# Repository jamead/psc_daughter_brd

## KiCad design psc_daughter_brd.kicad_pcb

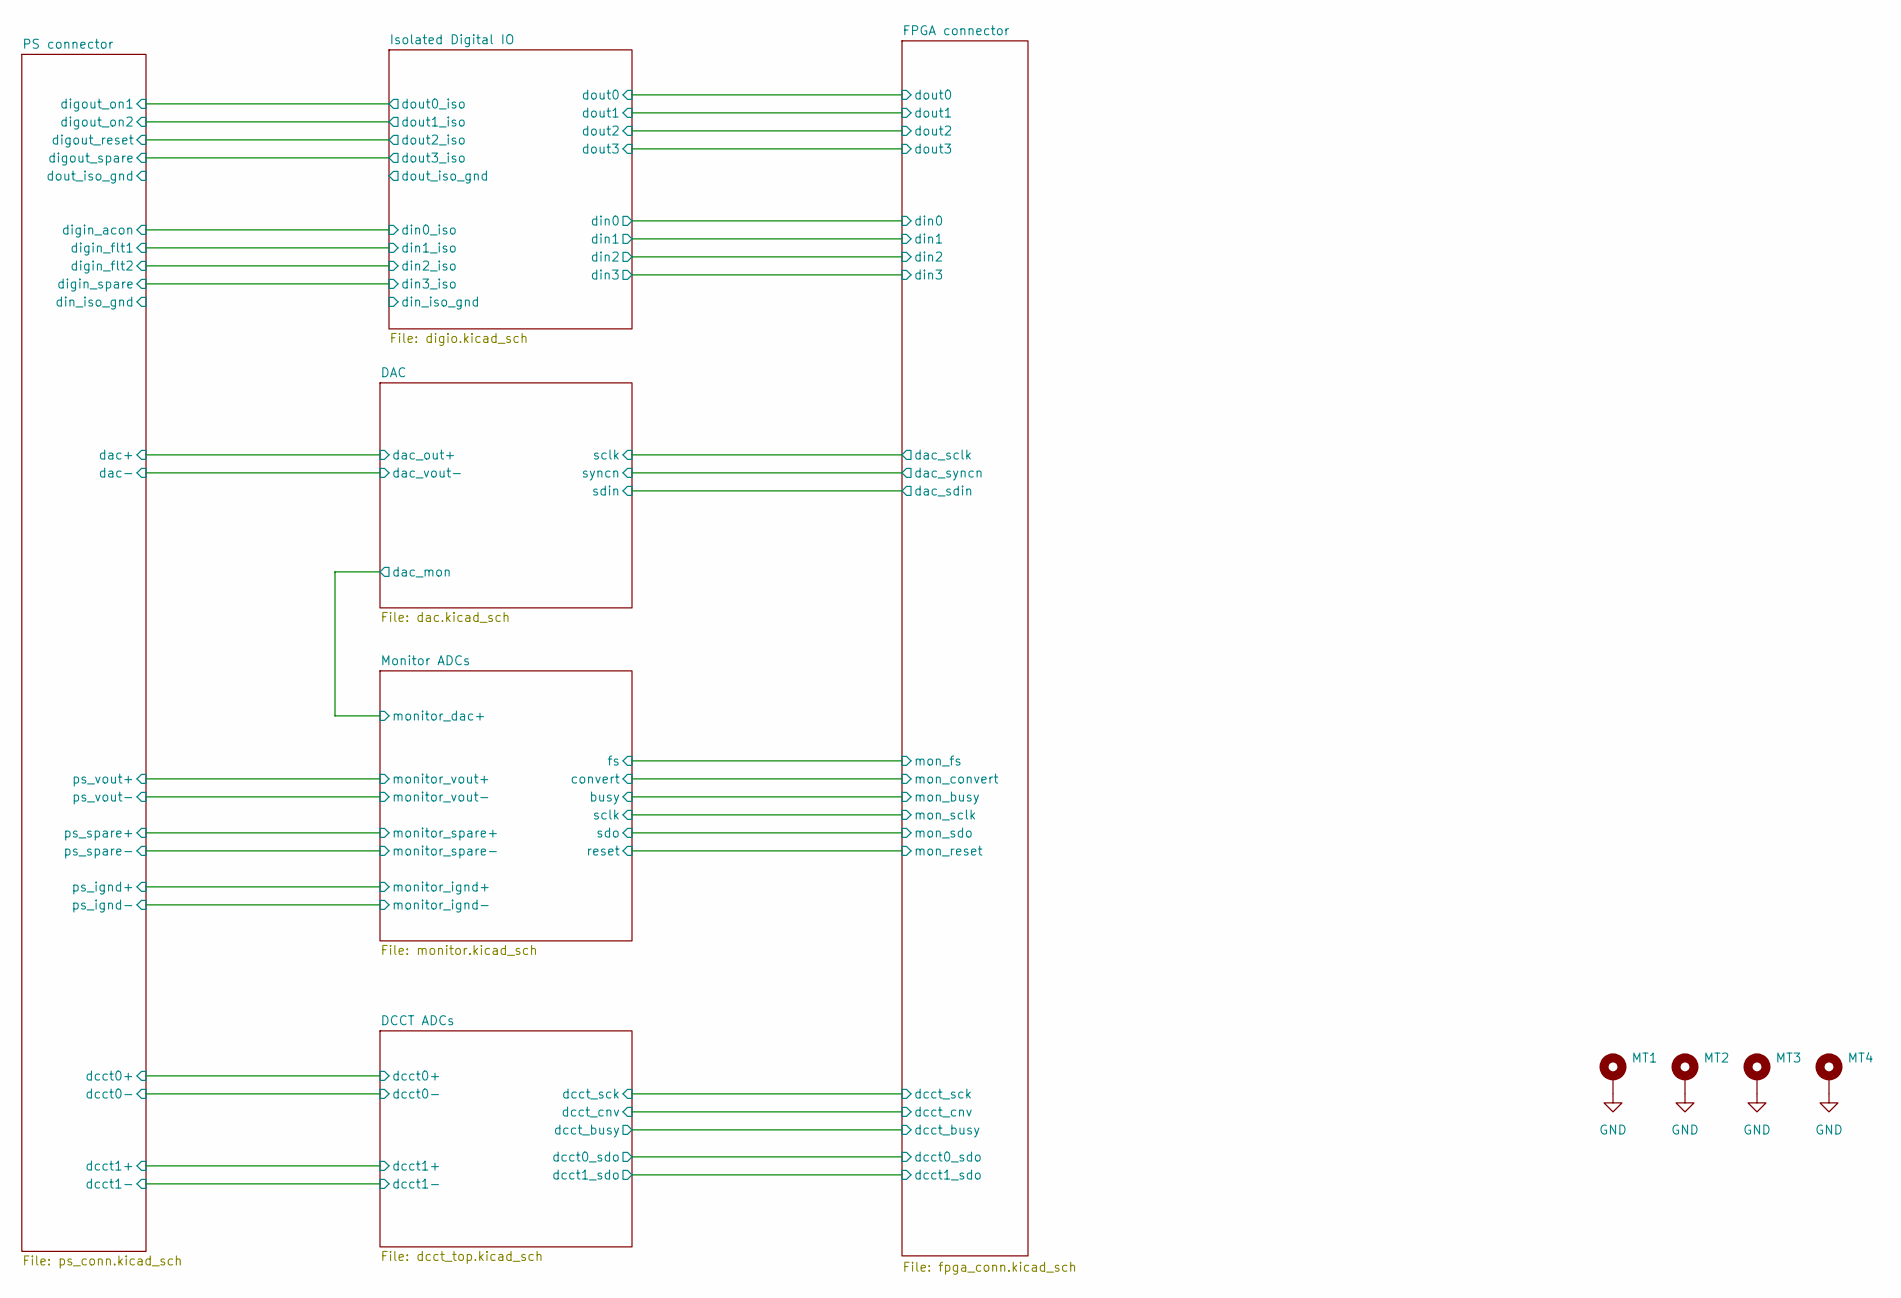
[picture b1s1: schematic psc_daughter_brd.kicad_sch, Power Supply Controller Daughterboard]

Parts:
MT1, MT2, MT3, MT4: MountingHole_Pad; MountingHole_3.2mm_M3_Pad_TopBottom

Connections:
GND: MT1.1, MT2.1, MT3.1, MT4.1; also elsewhere on the board

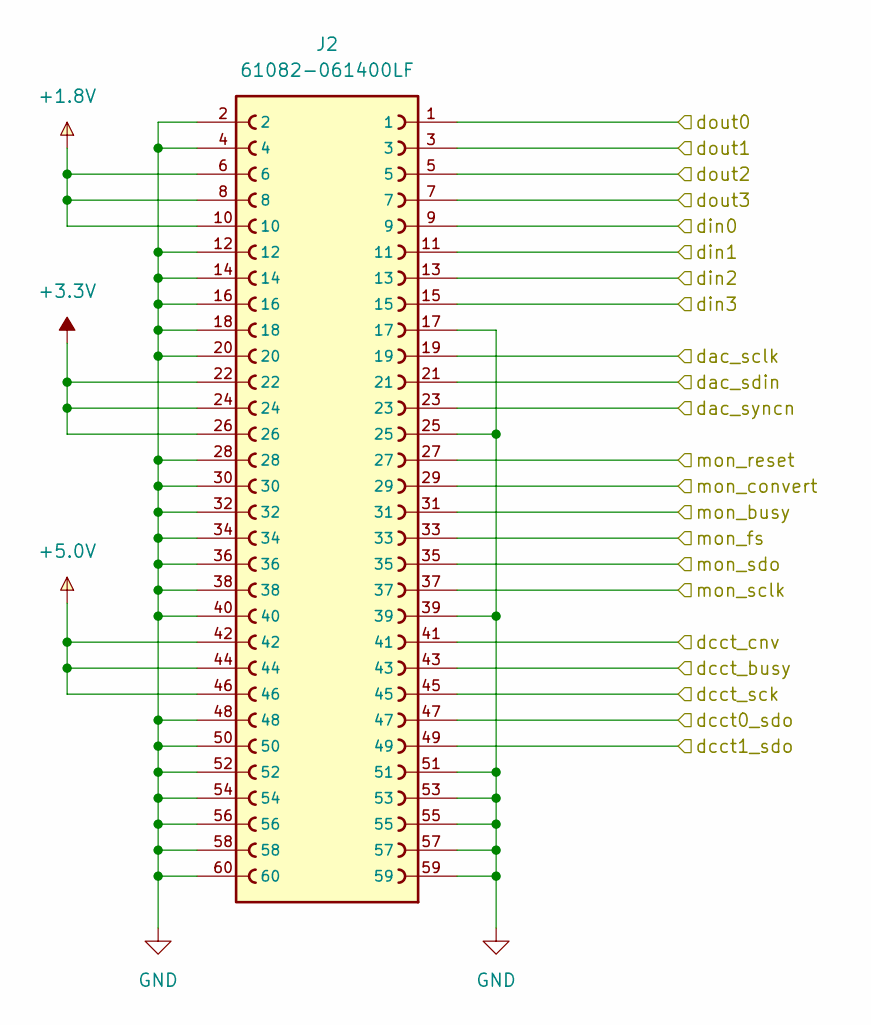
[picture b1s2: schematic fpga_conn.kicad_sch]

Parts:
J2: 61082-061400LF; AMPHENOL_61082-061400LF; PARTREV AS

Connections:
+1.8V: J2.6, J2.8, J2.10; also elsewhere on the board
+3.3V: J2.22, J2.24, J2.26; also elsewhere on the board
+5.0V: J2.42, J2.44, J2.46; also elsewhere on the board
/DAC/sclk: J2.19; also elsewhere on the board
/DAC/sdin: J2.21; also elsewhere on the board
/DAC/syncn: J2.23; also elsewhere on the board
/DCCT ADCs/dcct0_sdo: J2.47; also elsewhere on the board
/DCCT ADCs/dcct1_sdo: J2.49; also elsewhere on the board
/DCCT ADCs/dcct_busy: J2.43; also elsewhere on the board
/DCCT ADCs/dcct_cnv: J2.41; also elsewhere on the board
/DCCT ADCs/dcct_sck: J2.45; also elsewhere on the board
/FPGA connector/din0: J2.9; also elsewhere on the board
/FPGA connector/din1: J2.11; also elsewhere on the board
/FPGA connector/din2: J2.13; also elsewhere on the board
/FPGA connector/din3: J2.15; also elsewhere on the board
/FPGA connector/dout0: J2.1; also elsewhere on the board
/FPGA connector/dout1: J2.3; also elsewhere on the board
/FPGA connector/dout2: J2.5; also elsewhere on the board
/FPGA connector/dout3: J2.7; also elsewhere on the board
/FPGA connector/mon_busy: J2.31; also elsewhere on the board
/FPGA connector/mon_convert: J2.29; also elsewhere on the board
/FPGA connector/mon_fs: J2.33; also elsewhere on the board
/FPGA connector/mon_reset: J2.27; also elsewhere on the board
/FPGA connector/mon_sclk: J2.37; also elsewhere on the board
/FPGA connector/mon_sdo: J2.35; also elsewhere on the board
GND: J2.2, J2.4, J2.12, J2.14, J2.16, J2.17, J2.18, J2.20, J2.25, J2.28, J2.30, J2.32, J2.34, J2.36, J2.38, J2.39, J2.40, J2.48, J2.50, J2.51, J2.52, J2.53, J2.54, J2.55, J2.56, J2.57, J2.58, J2.59, J2.60; also elsewhere on the board

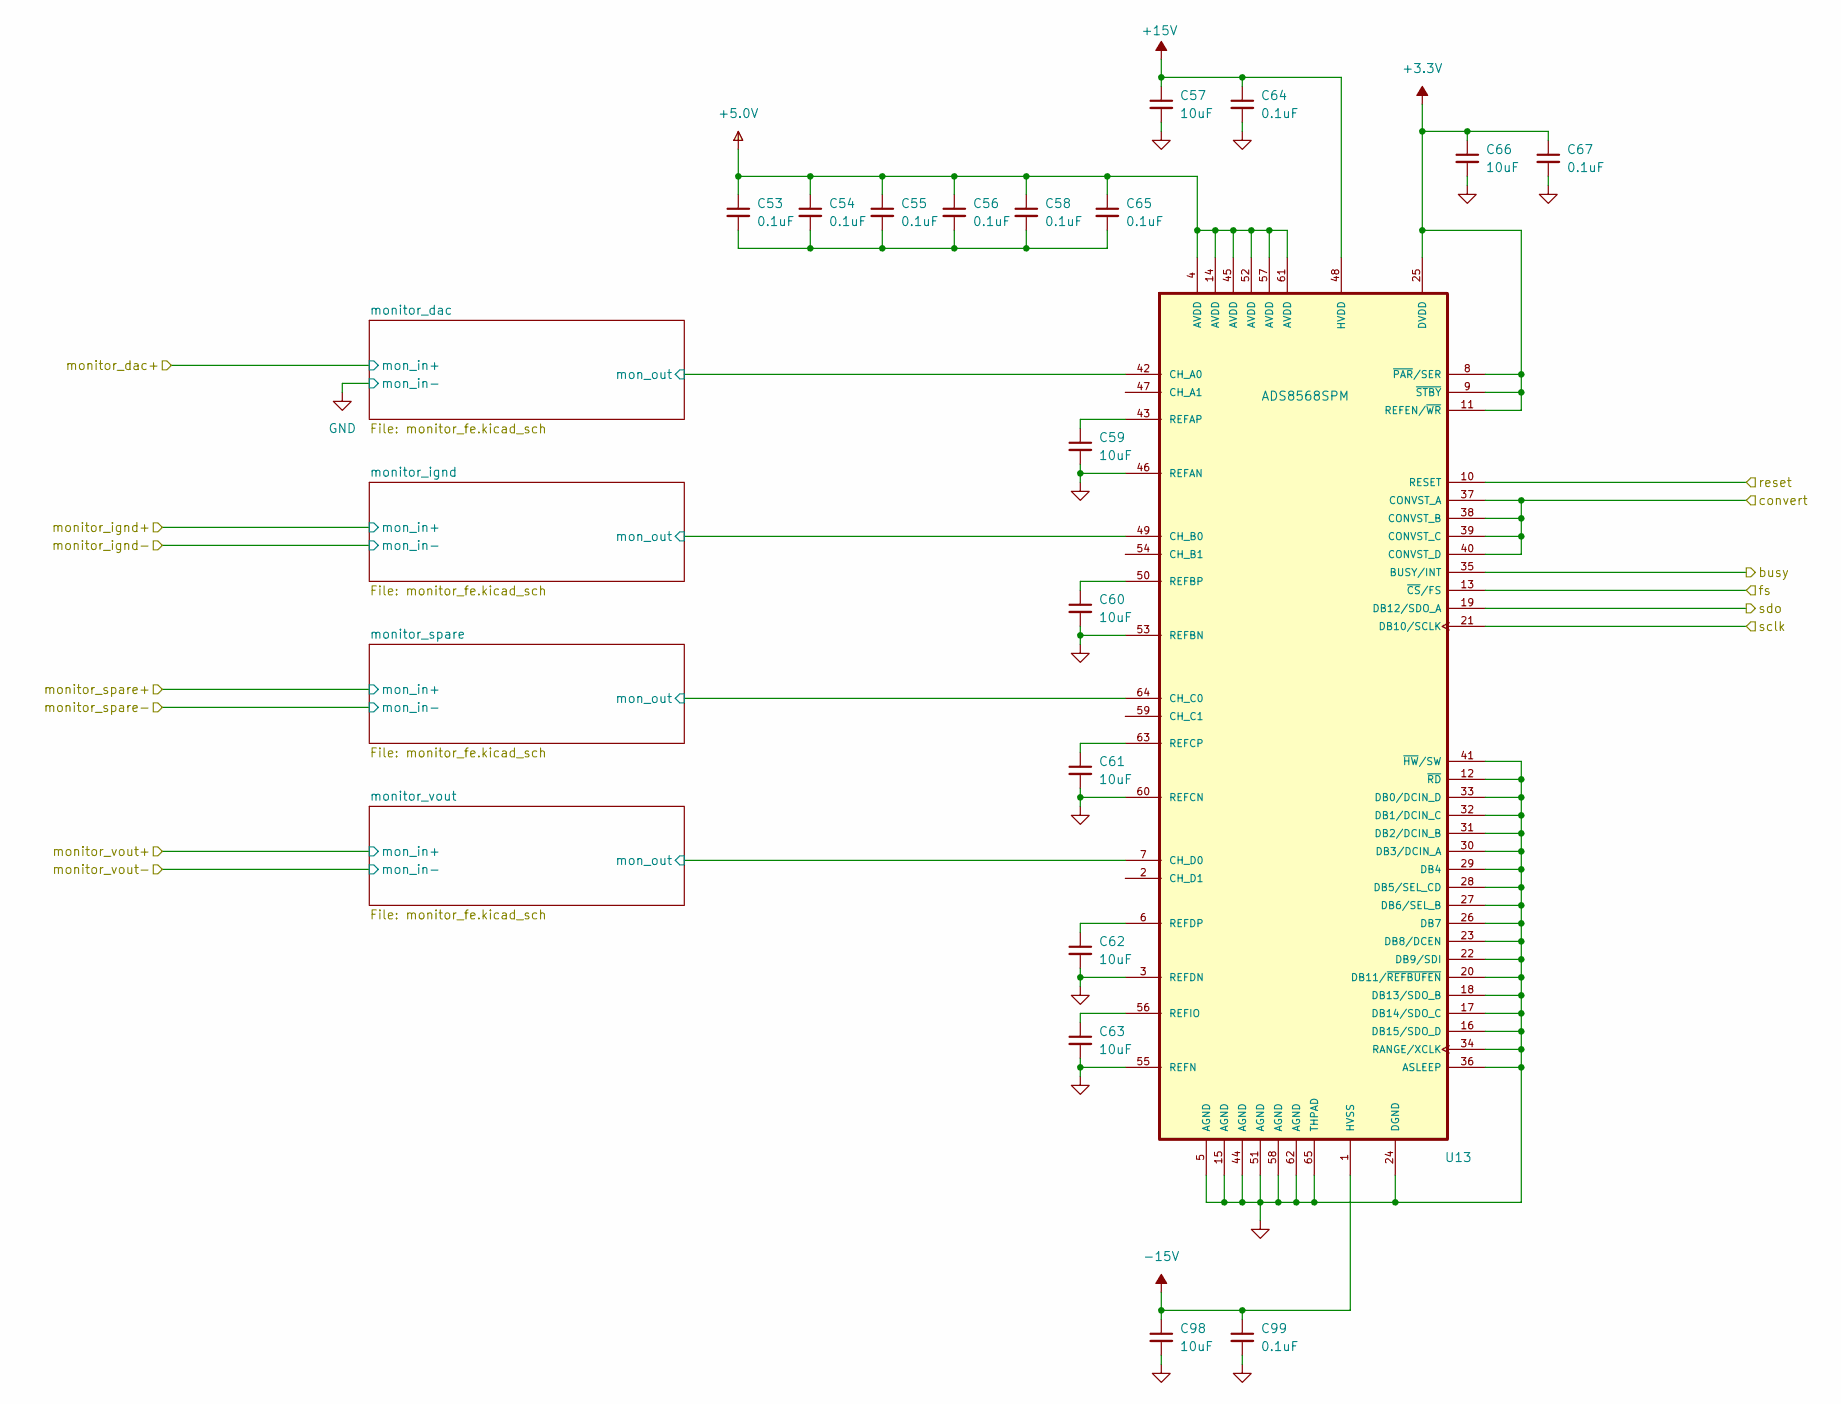
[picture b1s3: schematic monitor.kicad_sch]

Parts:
C53, C54, C55, C56, C58, C64, C65, C67, C99: 0.1uF; C_0402_1005Metric
C57, C59, C60, C61, C62, C63, C66, C98: 10uF; C_0603_1608Metric; Voltage 25V
U13: ADS8568SPM; QFP50P1200X1200X160-64N

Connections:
+3.3V: C66.1, C67.1, U13.8 (~PAR/SER), U13.9 (~STBY), U13.11 (REFEN/~WR), U13.25 (DVDD); also elsewhere on the board
+5.0V: C53.1, C54.1, C55.1, C56.1, C58.1, C65.1, U13.4 (AVDD), U13.14 (AVDD), U13.45 (AVDD), U13.52 (AVDD), U13.57 (AVDD), U13.61 (AVDD); also elsewhere on the board
+15V: C57.1, C64.1, U13.48 (HVDD); also elsewhere on the board
-15V: C98.1, C99.1, U13.1 (HVSS); also elsewhere on the board
/FPGA connector/mon_busy: U13.35 (BUSY/INT); also elsewhere on the board
/FPGA connector/mon_convert: U13.37 (CONVST_A), U13.38 (CONVST_B), U13.39 (CONVST_C), U13.40 (CONVST_D); also elsewhere on the board
/FPGA connector/mon_fs: U13.13 (~CS/FS); also elsewhere on the board
/FPGA connector/mon_reset: U13.10 (RESET); also elsewhere on the board
/FPGA connector/mon_sclk: U13.21 (DB10/SCLK); also elsewhere on the board
/FPGA connector/mon_sdo: U13.19 (DB12/SDO_A); also elsewhere on the board
/Monitor ADCs/monitor_dac/mon_out: U13.42 (CH_A0); also elsewhere on the board
/Monitor ADCs/monitor_ignd/mon_out: U13.49 (CH_B0); also elsewhere on the board
/Monitor ADCs/monitor_spare/mon_out: U13.64 (CH_C0); also elsewhere on the board
/Monitor ADCs/monitor_vout/mon_out: U13.7 (CH_D0); also elsewhere on the board
GND: C57.2, C59.2, C60.2, C61.2, C62.2, C63.2, C64.2, C66.2, C67.2, C98.2, C99.2, U13.3 (REFDN), U13.5 (AGND), U13.12 (~RD), U13.15 (AGND), U13.16 (DB15/SDO_D), U13.17 (DB14/SDO_C), U13.18 (DB13/SDO_B), U13.20 (DB11/~REFBUFEN), U13.22 (DB9/SDI), U13.23 (DB8/DCEN), U13.24 (DGND), U13.26 (DB7), U13.27 (DB6/SEL_B), U13.28 (DB5/SEL_CD), U13.29 (DB4), U13.30 (DB3/DCIN_A), U13.31 (DB2/DCIN_B), U13.32 (DB1/DCIN_C), U13.33 (DB0/DCIN_D), U13.34 (RANGE/XCLK), U13.36 (ASLEEP), U13.41 (~HW/SW), U13.44 (AGND), U13.46 (REFAN), U13.51 (AGND), U13.53 (REFBN), U13.55 (REFN), U13.58 (AGND), U13.60 (REFCN), U13.62 (AGND), U13.65 (THPAD); also elsewhere on the board
unnamed: C53.2, C54.2, C55.2, C56.2, C58.2, C65.2
unnamed: C59.1, U13.43 (REFAP)
unnamed: C60.1, U13.50 (REFBP)
unnamed: C61.1, U13.63 (REFCP)
unnamed: C62.1, U13.6 (REFDP)
unnamed: C63.1, U13.56 (REFIO)

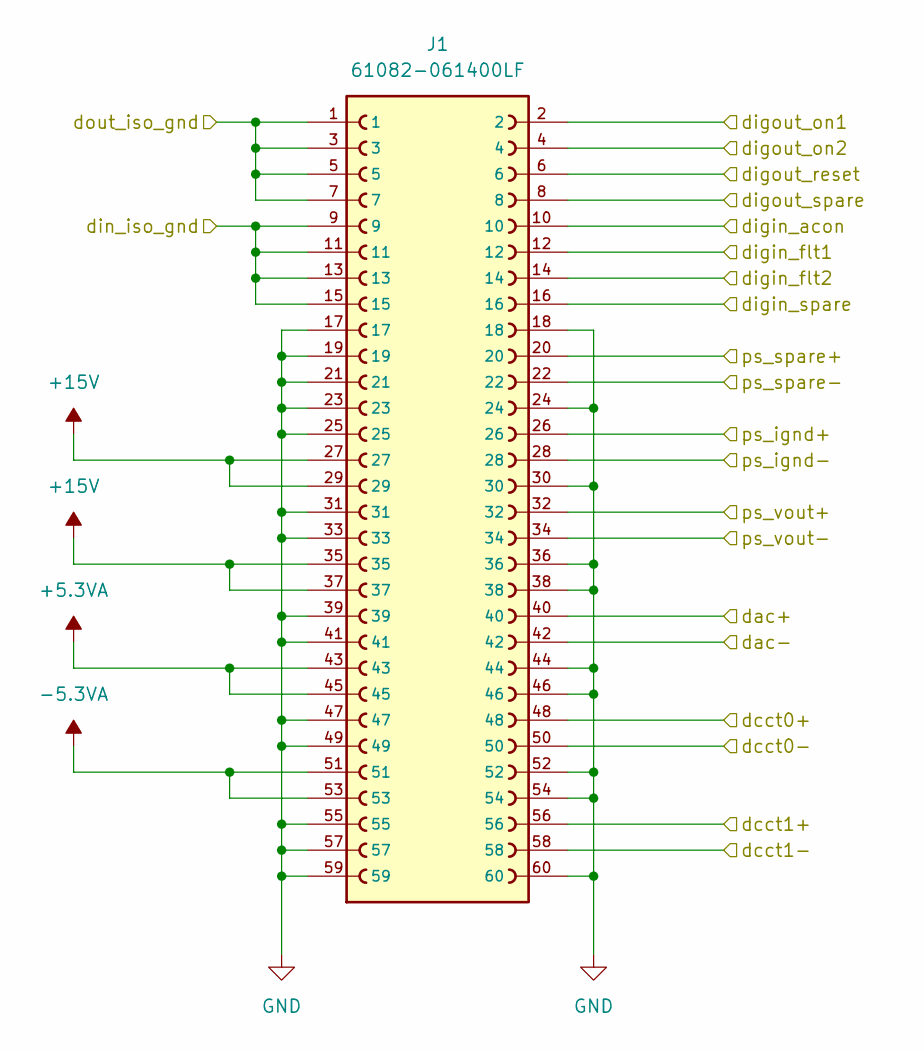
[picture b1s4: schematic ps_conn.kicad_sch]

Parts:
J1: 61082-061400LF; AMPHENOL_61082-061400LF; PARTREV AS

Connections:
+5.3VA: J1.43, J1.45; also elsewhere on the board
+15V: J1.27, J1.29, J1.35, J1.37; also elsewhere on the board
-5.3VA: J1.51, J1.53; also elsewhere on the board
/DAC/dac_out+: J1.40; also elsewhere on the board
/DAC/dac_vout-: J1.42; also elsewhere on the board
/DCCT ADCs/dcct0+: J1.48; also elsewhere on the board
/DCCT ADCs/dcct0-: J1.50; also elsewhere on the board
/DCCT ADCs/dcct1+: J1.56; also elsewhere on the board
/DCCT ADCs/dcct1-: J1.58; also elsewhere on the board
/Isolated Digital IO/din0_iso: J1.10; also elsewhere on the board
/Isolated Digital IO/din1_iso: J1.12; also elsewhere on the board
/Isolated Digital IO/din2_iso: J1.14; also elsewhere on the board
/Isolated Digital IO/din3_iso: J1.16; also elsewhere on the board
/Isolated Digital IO/dout0_iso: J1.2; also elsewhere on the board
/Isolated Digital IO/dout1_iso: J1.4; also elsewhere on the board
/Isolated Digital IO/dout2_iso: J1.6; also elsewhere on the board
/Isolated Digital IO/dout3_iso: J1.8; also elsewhere on the board
/Monitor ADCs/monitor_ignd+: J1.26; also elsewhere on the board
/Monitor ADCs/monitor_ignd-: J1.28; also elsewhere on the board
/Monitor ADCs/monitor_spare+: J1.20; also elsewhere on the board
/Monitor ADCs/monitor_spare-: J1.22; also elsewhere on the board
/Monitor ADCs/monitor_vout+: J1.32; also elsewhere on the board
/Monitor ADCs/monitor_vout-: J1.34; also elsewhere on the board
/PS connector/din_iso_gnd: J1.9, J1.11, J1.13, J1.15
/PS connector/dout_iso_gnd: J1.1, J1.3, J1.5, J1.7
GND: J1.17, J1.18, J1.19, J1.21, J1.23, J1.24, J1.25, J1.30, J1.31, J1.33, J1.36, J1.38, J1.39, J1.41, J1.44, J1.46, J1.47, J1.49, J1.52, J1.54, J1.55, J1.57, J1.59, J1.60; also elsewhere on the board

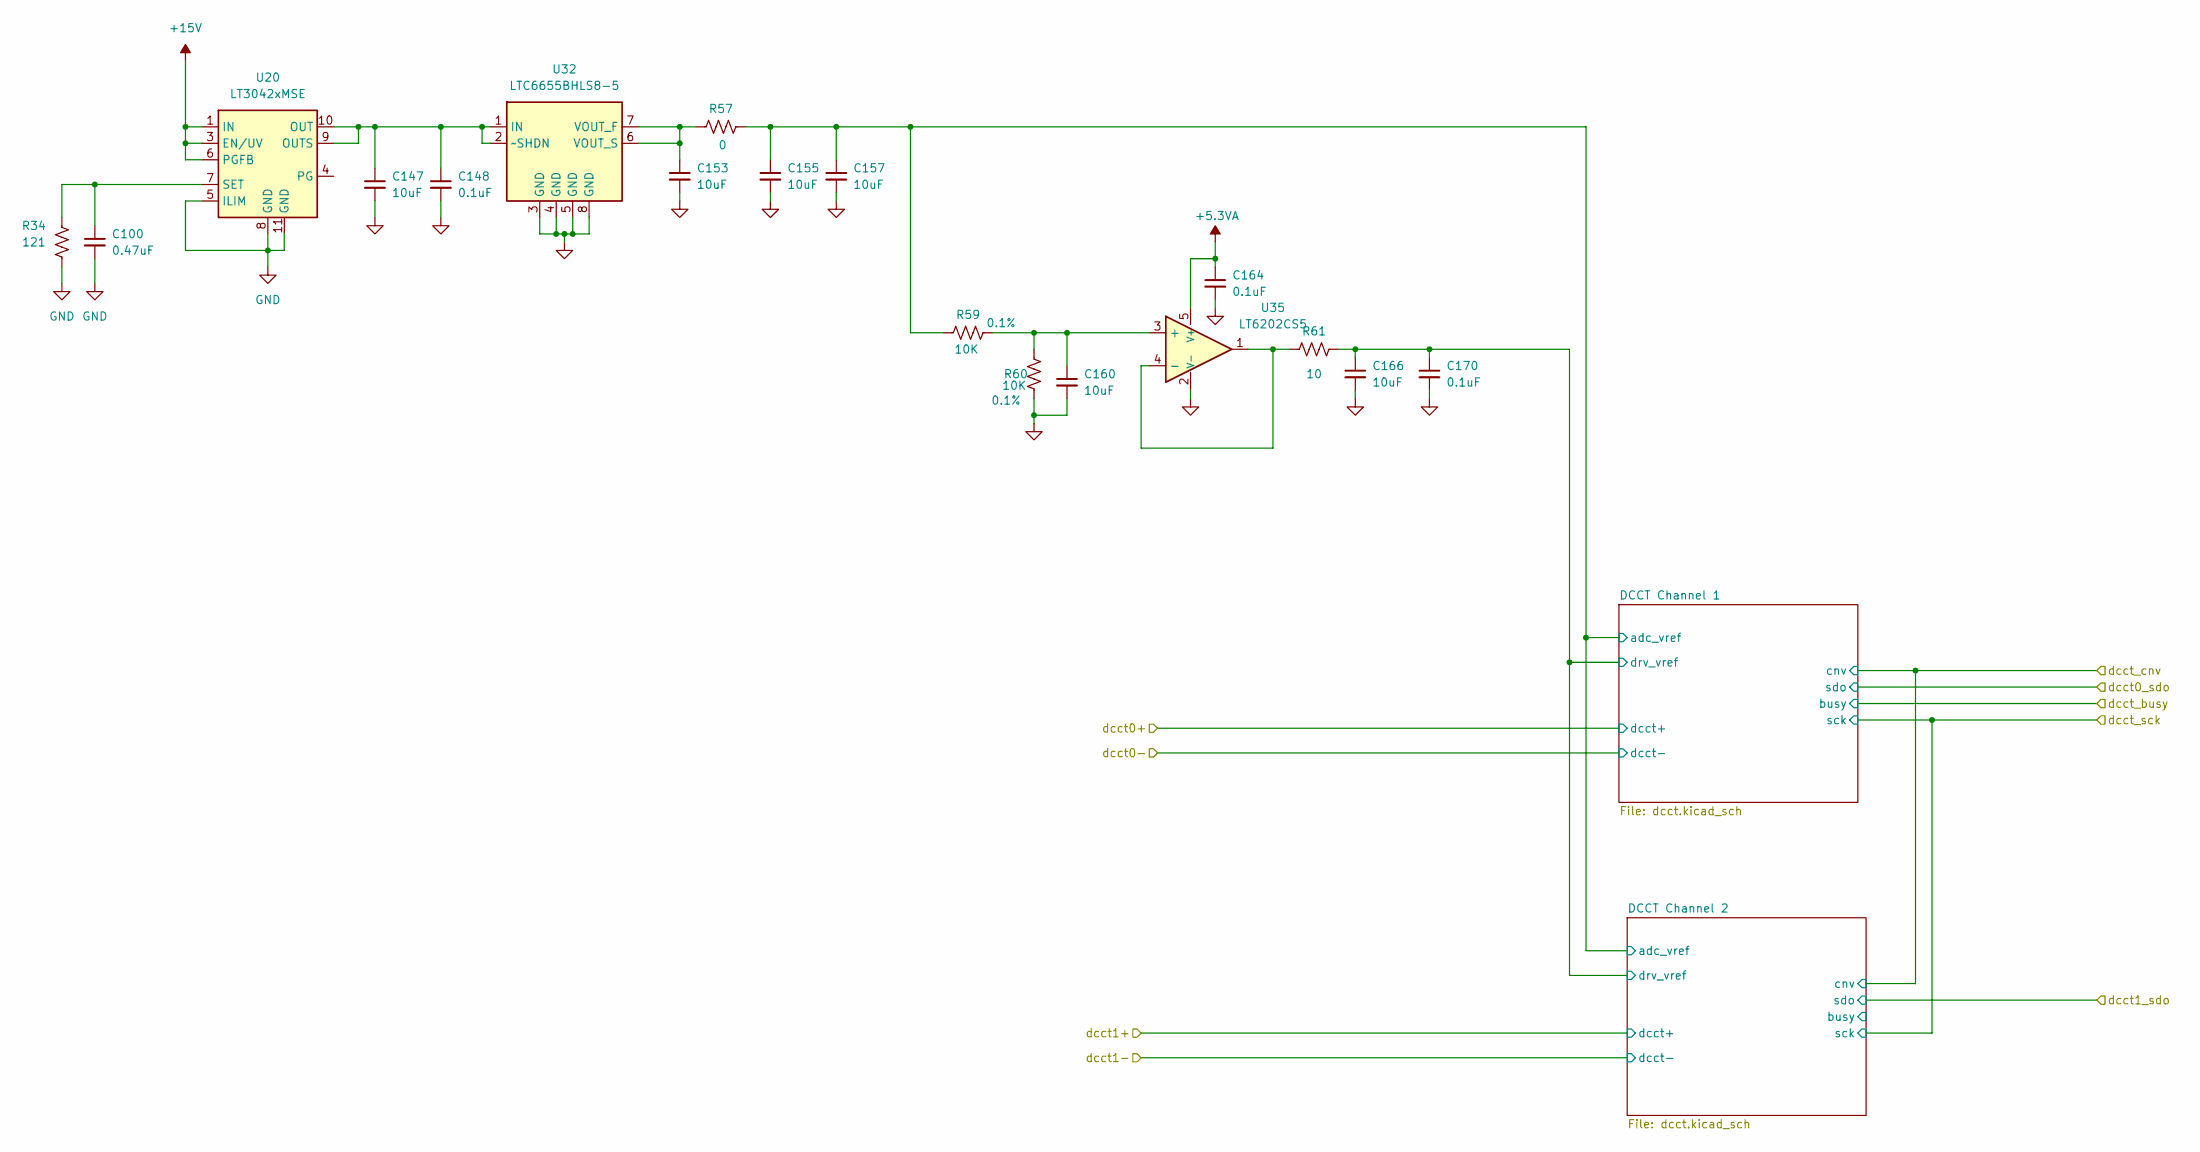
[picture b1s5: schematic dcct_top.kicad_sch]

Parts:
C100: 0.47uF; C_0402_1005Metric
C147, C153, C155, C157, C160, C166: 10uF; C_0603_1608Metric; Voltage 25V
C148, C164, C170: 0.1uF; C_0402_1005Metric
R34: 121; R_0402_1005Metric; Tolerance 1%
R57: 0; R_0402_1005Metric; Tolerance 1%
R59, R60: 10K; R_0402_1005Metric; Tolerance 0.1%
R61: 10; R_0402_1005Metric; Tolerance 1%
U20: LT3042xMSE; MSOP-10-1EP_3x3mm_P0.5mm_EP1.68x1.88mm
U32: LTC6655BHLS8-5; LTC6655
U35: LT6202CS5

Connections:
+5.3VA: C164.1, U35.5 (V+); also elsewhere on the board
+15V: U20.1 (IN), U20.2 (IN), U20.3 (EN/UV), U20.6 (PGFB); also elsewhere on the board
/DCCT ADCs/DCCT Channel 1/adc_vref: C155.1, C157.1, R57.1, R59.2; also elsewhere on the board
/DCCT ADCs/DCCT Channel 1/drv_vref: C166.1, C170.1, R61.1; also elsewhere on the board
GND: C100.2, C147.2, C148.2, C153.2, C155.2, C157.2, C160.2, C164.2, C166.2, C170.2, R34.1, R60.2, U20.5 (ILIM), U20.8 (GND), U20.11 (GND), U32.3 (GND), U32.4 (GND), U32.5 (GND), U32.8 (GND), U35.2 (V-); also elsewhere on the board
unnamed: C147.1, C148.1, U20.9 (OUTS), U20.10 (OUT), U32.1 (IN), U32.2 (~SHDN)
unnamed: C100.1, R34.2, U20.7 (SET)
unnamed: C153.1, R57.2, U32.6 (VOUT_S), U32.7 (VOUT_F)
unnamed: C160.1, R59.1, R60.1, U35.3 (+)
unnamed: R61.2, U35.1, U35.4 (-)

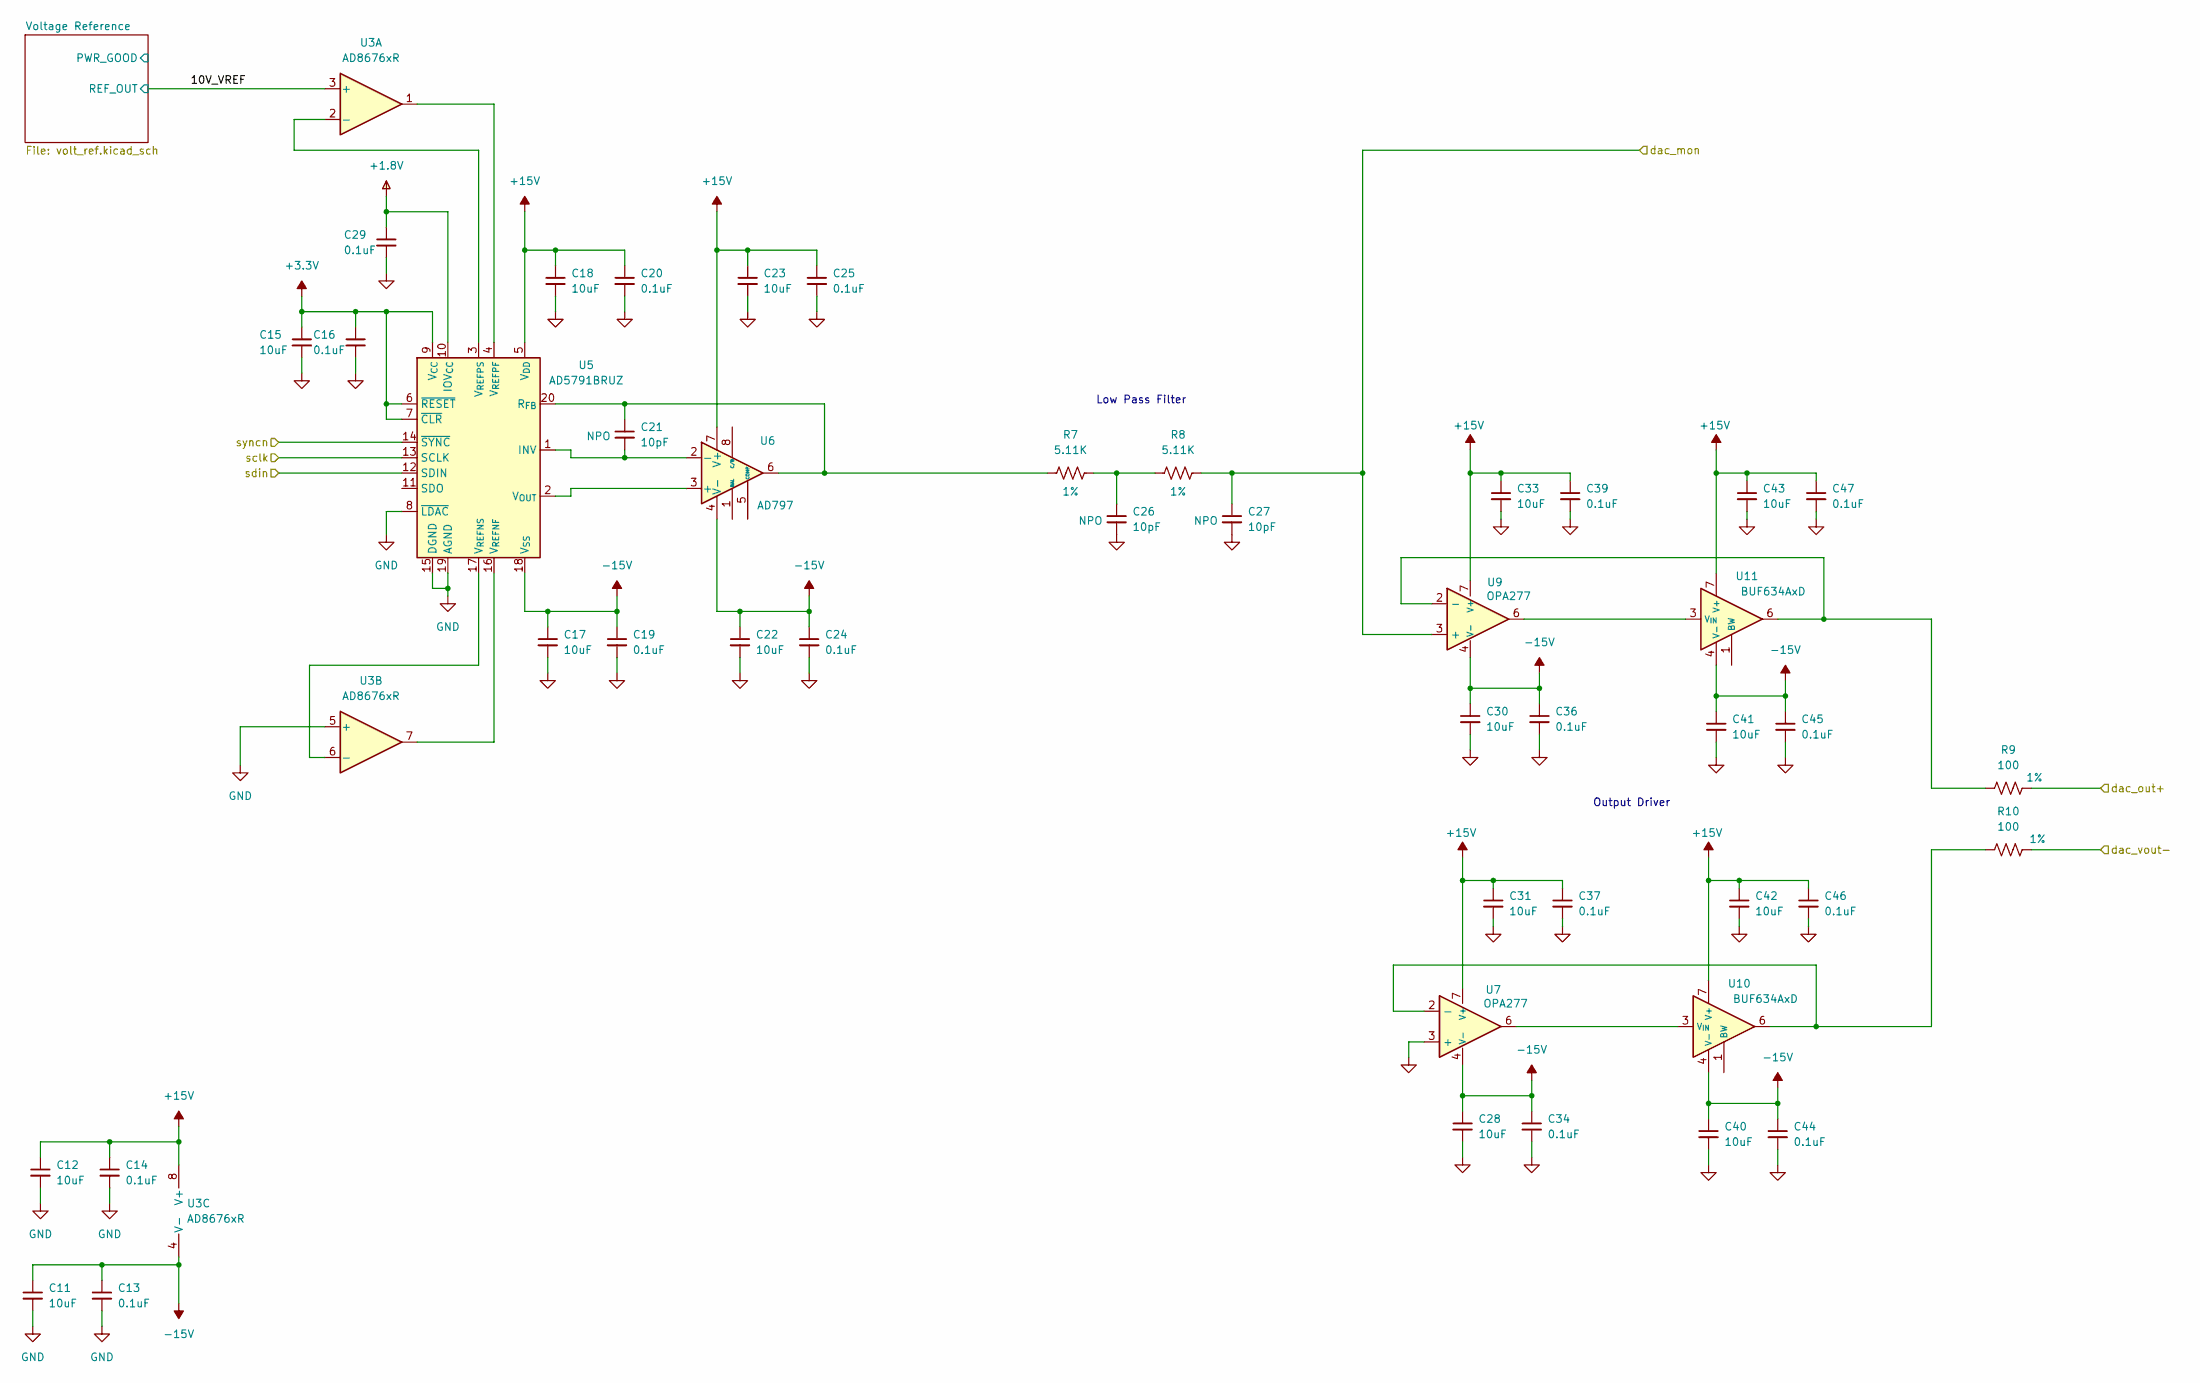
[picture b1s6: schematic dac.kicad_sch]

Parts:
C11, C12, C15, C17, C18, C22, C23, C28, C30, C31, C33, C40, C41, C42, C43: 10uF; C_0603_1608Metric; Voltage 25V
C13, C14, C16, C19, C20, C24, C25, C29, C34, C36, C37, C39, C44, C45, C46, C47: 0.1uF; C_0402_1005Metric
C21, C26, C27: 10pF; C_0402_1005Metric
R7, R8: 5.11K; R_0402_1005Metric; Tolerance 1%
R9, R10: 100; R_0603_1608Metric; Tolerance 1%
U3: AD8676xR; SOIC-8_3.9x4.9mm_P1.27mm
U5: AD5791BRUZ; TSSOP-20_4.4x6.5mm_P0.65mm
U6: AD797; SOIC-8_3.9x4.9mm_P1.27mm
U7, U9: OPA277; SOIC-8_3.9x4.9mm_P1.27mm
U10, U11: BUF634AxD; SOIC-8_3.9x4.9mm_P1.27mm

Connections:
+1.8V: C29.1, U5.10 (IOV_{CC}); also elsewhere on the board
+3.3V: C15.1, C16.1, U5.6 (~RESET), U5.7 (~CLR), U5.9 (V_{CC}); also elsewhere on the board
+15V: C12.1, C14.1, C18.1, C20.1, C23.1, C25.1, C31.1, C33.1, C37.1, C39.1, C42.1, C43.1, C46.1, C47.1, U3.8 (V+), U5.5 (V_{DD}), U6.7 (V+), U7.7 (V+), U9.7 (V+), U10.7 (V+), U11.7 (V+); also elsewhere on the board
-15V: C11.1, C13.1, C17.1, C19.1, C22.1, C24.1, C28.1, C30.1, C34.1, C36.1, C40.1, C41.1, C44.1, C45.1, U3.4 (V-), U5.18 (V_{SS}), U6.4 (V-), U7.4 (V-), U9.4 (V-), U10.4 (V-), U11.4 (V-); also elsewhere on the board
/DAC/Voltage Reference/REF_OUT: U3.3 (+); also elsewhere on the board
/DAC/dac_mon: C27.1, R8.2, U9.3 (+); also elsewhere on the board
/DAC/dac_out+: R9.2; also elsewhere on the board
/DAC/dac_vout-: R10.2; also elsewhere on the board
/DAC/sclk: U5.13 (SCLK); also elsewhere on the board
/DAC/sdin: U5.12 (SDIN); also elsewhere on the board
/DAC/syncn: U5.14 (~SYNC); also elsewhere on the board
GND: C11.2, C12.2, C13.2, C14.2, C15.2, C16.2, C17.2, C18.2, C19.2, C20.2, C22.2, C23.2, C24.2, C25.2, C26.2, C27.2, C28.2, C29.2, C30.2, C31.2, C33.2, C34.2, C36.2, C37.2, C39.2, C40.2, C41.2, C42.2, C43.2, C44.2, C45.2, C46.2, C47.2, U3.5 (+), U5.8 (~LDAC), U5.15 (DGND), U5.19 (AGND), U7.3 (+); also elsewhere on the board
unnamed: C26.1, R7.2, R8.1
unnamed: U3.2 (-), U5.3 (V_{REFPS})
unnamed: U3.6 (-), U5.17 (V_{REFNS})
unnamed: C21.2, U5.1 (INV), U6.2 (-)
unnamed: C21.1, R7.1, U5.20 (R_{FB}), U6.6
unnamed: U5.2 (V_{OUT}), U6.3 (+)
unnamed: U3.7, U5.16 (V_{REFNF})
unnamed: U3.1, U5.4 (V_{REFPF})
unnamed: R10.1, U7.2 (-), U10.6
unnamed: R9.1, U9.2 (-), U11.6
unnamed: U7.6, U10.3 (V_{IN})
unnamed: U9.6, U11.3 (V_{IN})

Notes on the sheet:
Output Driver
Low Pass Filter

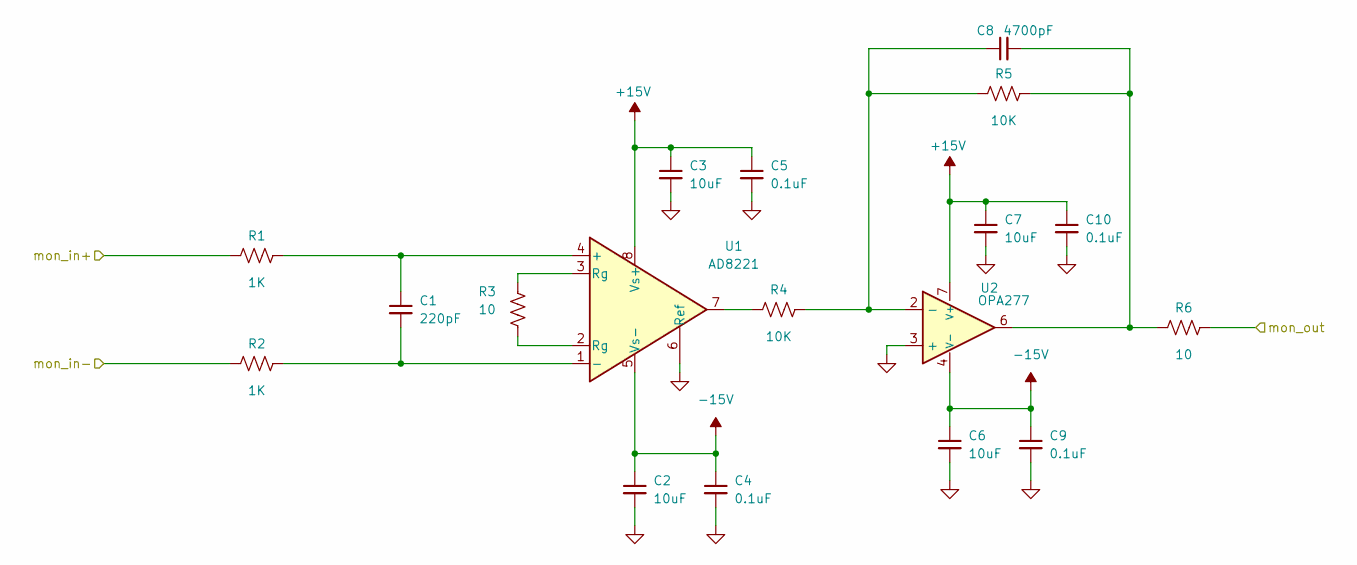
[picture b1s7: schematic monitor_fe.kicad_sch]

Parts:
C1: 220pF; C_0402_1005Metric
C2, C3, C6, C7: 10uF; C_0603_1608Metric; Voltage 25V
C4, C5, C9, C10: 0.1uF; C_0402_1005Metric
C8: 4700pF; C_0402_1005Metric
R1, R2: 1K; R_0402_1005Metric; Tolerance 1%
R3, R6: 10; R_0402_1005Metric; Tolerance 1%
R4, R5: 10K; R_0402_1005Metric; Tolerance 1%
U1: AD8221; SOIC127P600X175-8N
U2: OPA277; SOIC-8_3.9x4.9mm_P1.27mm

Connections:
+15V: C3.1, C5.1, C7.1, C10.1, U1.8 (Vs+), U2.7 (V+); also elsewhere on the board
-15V: C2.1, C4.1, C6.1, C9.1, U1.5 (Vs-), U2.4 (V-); also elsewhere on the board
/Monitor ADCs/monitor_ignd+: R1.2; also elsewhere on the board
/Monitor ADCs/monitor_ignd-: R2.2; also elsewhere on the board
/Monitor ADCs/monitor_ignd/mon_out: R6.1; also elsewhere on the board
GND: C2.2, C3.2, C4.2, C5.2, C6.2, C7.2, C9.2, C10.2, U1.6 (Ref), U2.3 (+); also elsewhere on the board
unnamed: C8.2, R5.1, R6.2, U2.6
unnamed: R3.1, U1.2 (Rg)
unnamed: R3.2, U1.3 (Rg)
unnamed: R4.2, U1.7
unnamed: C1.1, R1.1, U1.4 (+)
unnamed: C1.2, R2.1, U1.1 (-)
unnamed: C8.1, R4.1, R5.2, U2.2 (-)

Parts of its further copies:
C68, C78, C88: 220pF; C_0402_1005Metric
C69, C70, C73, C74, C79, C80, C83, C84, C89, C90, C93, C94: 10uF; C_0603_1608Metric; Voltage 25V
C71, C72, C76, C77, C81, C82, C86, C87, C91, C92, C96, C97: 0.1uF; C_0402_1005Metric
C75, C85, C95: 4700pF; C_0402_1005Metric
R16, R17, R22, R23, R28, R29: 1K; R_0402_1005Metric; Tolerance 1%
R18, R21, R24, R27, R30, R33: 10; R_0402_1005Metric; Tolerance 1%
R19, R20, R25, R26, R31, R32: 10K; R_0402_1005Metric; Tolerance 1%
U14, U16, U18: AD8221; SOIC127P600X175-8N
U15, U17, U19: OPA277; SOIC-8_3.9x4.9mm_P1.27mm

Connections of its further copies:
+15V: C70.1, C72.1, C74.1, C77.1, C80.1, C82.1, C84.1, C87.1, C90.1, C92.1, C94.1, C97.1, U14.8 (Vs+), U15.7 (V+), U16.8 (Vs+), U17.7 (V+), U18.8 (Vs+), U19.7 (V+); also elsewhere on the board
-15V: C69.1, C71.1, C73.1, C76.1, C79.1, C81.1, C83.1, C86.1, C89.1, C91.1, C93.1, C96.1, U14.5 (Vs-), U15.4 (V-), U16.5 (Vs-), U17.4 (V-), U18.5 (Vs-), U19.4 (V-); also elsewhere on the board
/DAC/dac_mon: R16.2; also elsewhere on the board
/Monitor ADCs/monitor_dac/mon_out: R21.1; also elsewhere on the board
/Monitor ADCs/monitor_spare+: R22.2; also elsewhere on the board
/Monitor ADCs/monitor_spare-: R23.2; also elsewhere on the board
/Monitor ADCs/monitor_spare/mon_out: R27.1; also elsewhere on the board
/Monitor ADCs/monitor_vout+: R28.2; also elsewhere on the board
/Monitor ADCs/monitor_vout-: R29.2; also elsewhere on the board
/Monitor ADCs/monitor_vout/mon_out: R33.1; also elsewhere on the board
GND: C69.2, C70.2, C71.2, C72.2, C73.2, C74.2, C76.2, C77.2, C79.2, C80.2, C81.2, C82.2, C83.2, C84.2, C86.2, C87.2, C89.2, C90.2, C91.2, C92.2, C93.2, C94.2, C96.2, C97.2, R17.2, U14.6 (Ref), U15.3 (+), U16.6 (Ref), U17.3 (+), U18.6 (Ref), U19.3 (+); also elsewhere on the board
unnamed: C75.2, R20.1, R21.2, U15.6
unnamed: C85.2, R26.1, R27.2, U17.6
unnamed: C95.2, R32.1, R33.2, U19.6
unnamed: R18.1, U14.2 (Rg)
unnamed: R18.2, U14.3 (Rg)
unnamed: R19.2, U14.7
unnamed: R24.1, U16.2 (Rg)
unnamed: R24.2, U16.3 (Rg)
unnamed: R25.2, U16.7
unnamed: R30.1, U18.2 (Rg)
unnamed: R30.2, U18.3 (Rg)
unnamed: R31.2, U18.7
unnamed: C68.1, R16.1, U14.4 (+)
unnamed: C68.2, R17.1, U14.1 (-)
unnamed: C75.1, R19.1, R20.2, U15.2 (-)
unnamed: C78.1, R22.1, U16.4 (+)
unnamed: C78.2, R23.1, U16.1 (-)
unnamed: C85.1, R25.1, R26.2, U17.2 (-)
unnamed: C88.1, R28.1, U18.4 (+)
unnamed: C88.2, R29.1, U18.1 (-)
unnamed: C95.1, R31.1, R32.2, U19.2 (-)
